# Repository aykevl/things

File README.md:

# Sandbox for electronics projects

This is my personal stash of small electronics projects, usually written using [TinyGo](https://tinygo.org).

I won't guarantee anything about it. All I can say is that it did work for me at some point and I like sharing what I made. Many things are written once and then mostly forgotten so I probably won't provide any support for any of the code.

## License

Feel free to use this code however you wish (in other words, you can treat it as public domain). Especially for small parts I won't mind if you just copy it in your project. For larger pieces of code or if you copy a project entirely, I would appreciate attribution somewhere (but it's not required).

If you prefer having an actual license for legal reasons, you can use the [MIT license](https://opensource.org/license/mit/) - but again, the code is public domain so no need to actually use this:

```
Copyright 2023 Ayke van Laethem

Permission is hereby granted, free of charge, to any person obtaining a
copy of this software and associated documentation files (the
“Software”), to deal in the Software without restriction, including
without limitation the rights to use, copy, modify, merge, publish,
distribute, sublicense, and/or sell copies of the Software, and to
permit persons to whom the Software is furnished to do so, subject to
the following conditions:

The above copyright notice and this permission notice shall be included
in all copies or substantial portions of the Software.

THE SOFTWARE IS PROVIDED “AS IS”, WITHOUT WARRANTY OF ANY KIND, EXPRESS
OR IMPLIED, INCLUDING BUT NOT LIMITED TO THE WARRANTIES OF
MERCHANTABILITY, FITNESS FOR A PARTICULAR PURPOSE AND NONINFRINGEMENT.
IN NO EVENT SHALL THE AUTHORS OR COPYRIGHT HOLDERS BE LIABLE FOR ANY
CLAIM, DAMAGES OR OTHER LIABILITY, WHETHER IN AN ACTION OF CONTRACT,
TORT OR OTHERWISE, ARISING FROM, OUT OF OR IN CONNECTION WITH THE
SOFTWARE OR THE USE OR OTHER DEALINGS IN THE SOFTWARE.
```

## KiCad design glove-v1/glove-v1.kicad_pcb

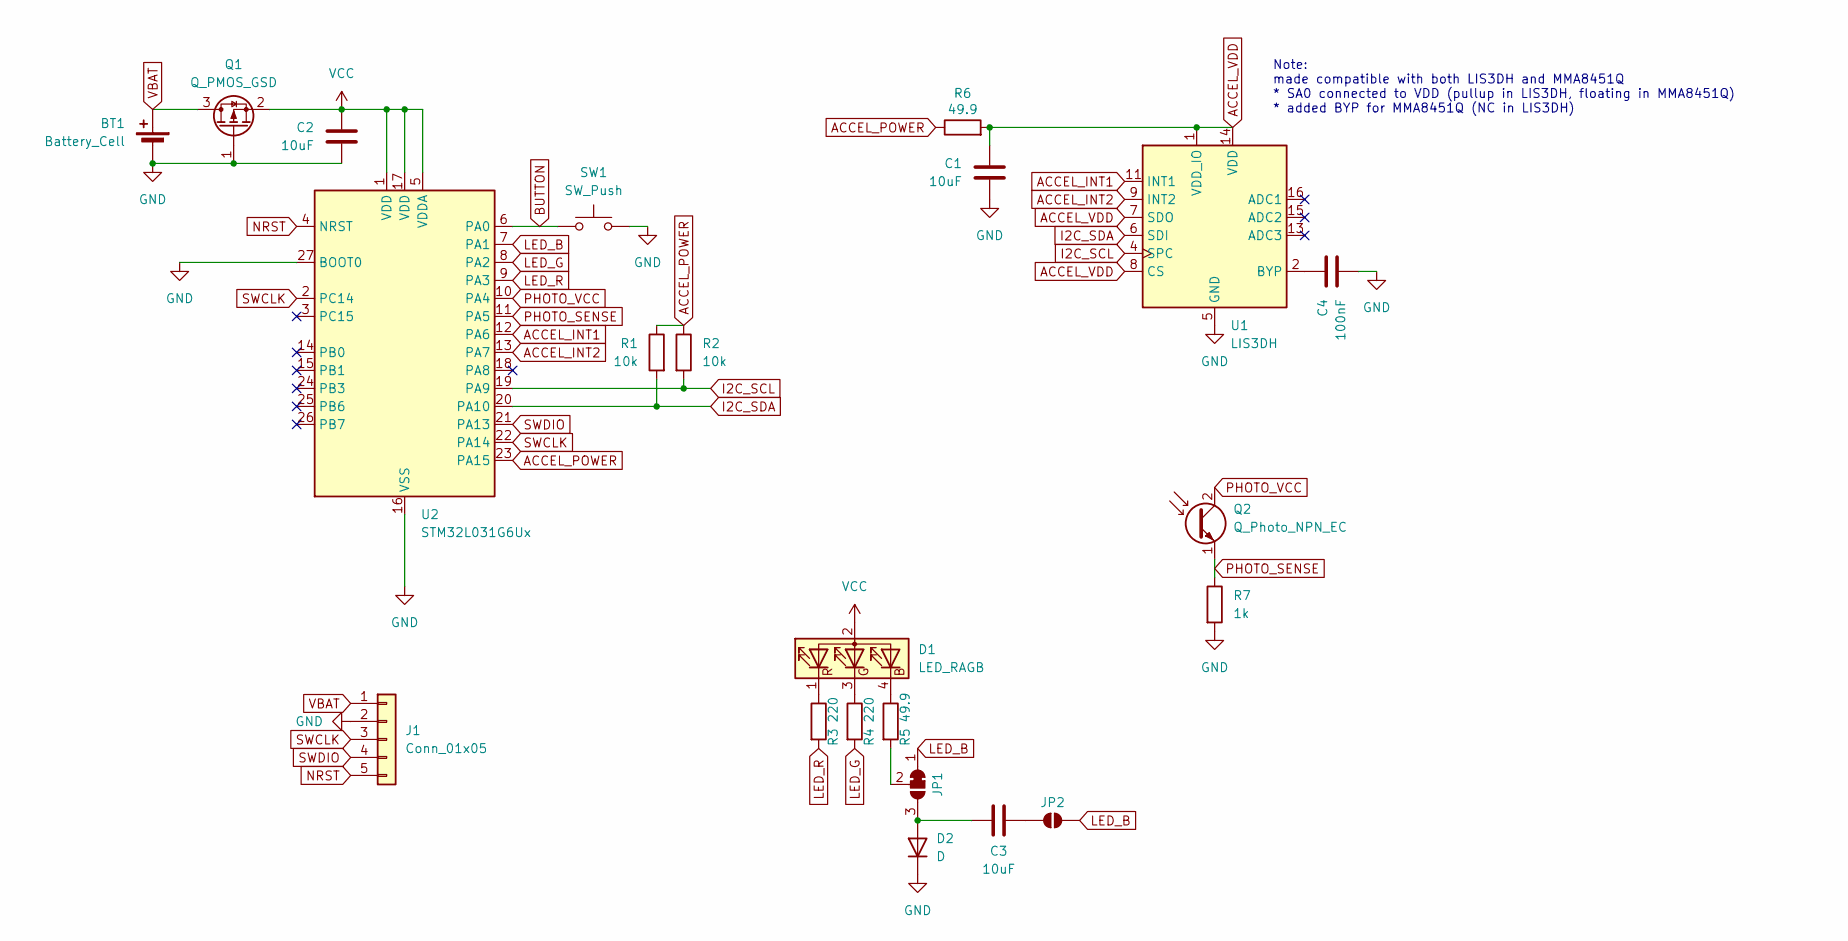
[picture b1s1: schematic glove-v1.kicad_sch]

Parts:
BT1: Battery_Cell; MY-1220-03; LCSC C964818
C1, C2, C3: 10uF; C_0402_1005Metric; LCSC C15525
C4: 100nF; C_0402_1005Metric; LCSC C1525
D1: LED_RAGB
D2: D; D_SOD-523; LCSC C2128
J1: Conn_01x05; ProgramHeader
JP1: SolderJumper-3_P1.3mm_Bridged12_RoundedPad1.0x1.5mm
JP2: SolderJumper-2_P1.3mm_Open_RoundedPad1.0x1.5mm
Q1: Q_PMOS_GSD; SOT-23; LCSC C427391
Q2: Q_Photo_NPN_EC; LED_0603_1608Metric; LCSC C20416370
R1, R2: 10k; R_0402_1005Metric; LCSC C25744
R3, R4: 220; R_0402_1005Metric; LCSC C25091
R5, R6: 49.9; R_0402_1005Metric; LCSC C25120
R7: 1k; R_0402_1005Metric; LCSC C11702
SW1: SW_Push; SW_Push_SPST_NO_Alps_SKRK; LCSC C720477
U1: LIS3DH; LGA-16_3x3mm_P0.5mm_LayoutBorder3x5y; LCSC C15134
U2: STM32L031G6Ux; QFN-28_4x4mm_P0.5mm; LCSC C96514

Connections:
ACCEL_INT1: U1.11 (INT1), U2.12 (PA6)
ACCEL_INT2: U1.9 (INT2), U2.13 (PA7)
ACCEL_POWER: R1.1, R2.1, R6.1, U2.23 (PA15)
ACCEL_VDD: C1.1, R6.2, U1.1 (VDD_IO), U1.7 (SDO), U1.8 (CS), U1.14 (VDD)
BUTTON: SW1.2, U2.6 (PA0)
GND: BT1.2 (-), C1.2, C2.2, C4.2, D2.1 (K), J1.2, Q1.1 (G), R7.2, SW1.1, U1.5 (GND), U1.10 (GND), U1.12 (GND), U2.16 (VSS), U2.27 (BOOT0), U2.28 (VSS)
I2C_SCL: R2.2, U1.4 (SPC), U2.19 (PA9)
I2C_SDA: R1.2, U1.6 (SDI), U2.20 (PA10)
LED_B: JP1.1 (A), JP2.2 (B), U2.7 (PA1)
LED_G: R4.2, U2.8 (PA2)
LED_R: R3.2, U2.9 (PA3)
NRST: J1.5, U2.4 (NRST)
unnamed: D1.4 (BK), R5.1
unnamed: D1.3 (GK), R4.1
unnamed: D1.1 (RK), R3.1
unnamed: C3.1, D2.2 (A), JP1.3 (B)
unnamed: JP1.2 (C), R5.2
unnamed: C3.2, JP2.1 (A)
unnamed: C4.1, U1.2 (BYP)
PHOTO_SENSE: Q2.1 (E), R7.1, U2.11 (PA5)
PHOTO_VCC: Q2.2 (C), U2.10 (PA4)
SWCLK: J1.3, U2.2 (PC14), U2.22 (PA14)
SWDIO: J1.4, U2.21 (PA13)
VBAT: BT1.1 (+), J1.1, Q1.3 (D)
VCC: C2.1, D1.2 (A), Q1.2 (S), U2.1 (VDD), U2.5 (VDDA), U2.17 (VDD)

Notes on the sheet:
Note: made compatible with both LIS3DH and MMA8451Q * SA0 connected to VDD (pullup in LIS3DH, floating in MMA8451Q) * added BYP for MMA8451Q (NC in LIS3DH)

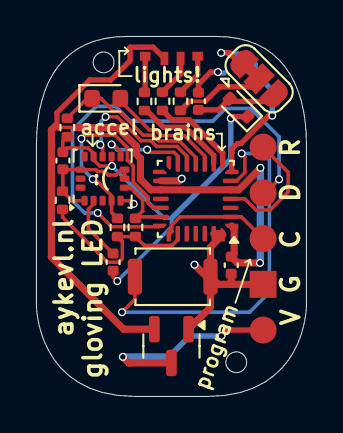
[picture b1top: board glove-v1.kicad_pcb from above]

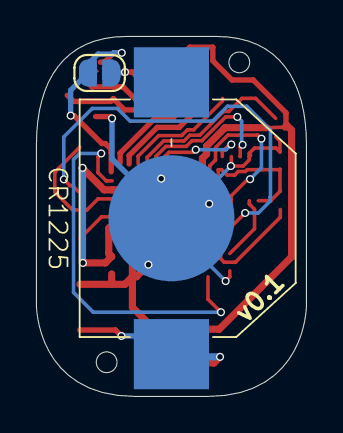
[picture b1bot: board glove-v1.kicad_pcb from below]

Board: 2 copper layers, 15.0 x 20.0 mm, 22 parts (2 on the bottom side), 25 nets.

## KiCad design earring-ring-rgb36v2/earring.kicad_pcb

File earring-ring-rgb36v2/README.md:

# 36-LED RGB earrings

These earrings are the successor to my previous [36-LED earrings](../earring-ring-rgb36). The main changes are the addition of a microphone and a second button. The software has also been greatly extended with many new animation patterns.

## Updating firmware

For writing the firmware, you will need an SWD programmer. Both [ST-Link](https://www.aliexpress.com/w/wholesale-st%2525252dlink-v2.html) and DAPLink programmers have been tested and work fine. You can even use a [Raspberry Pi Pico with a special firmware](https://github.com/raspberrypi/debugprobe/releases) as a [programmer](https://pip-assets.raspberrypi.com/categories/610-raspberry-pi-pico/documents/RP-008276-DS-1-getting-started-with-pico.pdf#page=19), use GP2 as SWCLK and GP3 as SWDIO.

You can connect the programmer as indicated on the PCB itself. Specifically:

  * Connect VCC to 3.3V, or don't connect it if you have a battery inserted (make sure to _never_ connect VCC when a battery is inserted!).
  * Connect GND to the programmer GND.
  * Connect SWC to the SWCLK pin on the programmer.
  * Connect SWD to the SWDIO pin on the programmer.

You normally don't need to connect RST, but it is exposed since it's possible to put the chip in a state where it doesn't respond to programming anymore an you need to briefly connect RST to GND to reset it.

I found the easiest way to program these earrings is using a clip with pogo-pins, like [this one](https://nl.aliexpress.com/item/1005006712952020.html) (2.54mm distance, single row, 4 or 5 pins depending on needs). It makes quick iteration much easier. However, you may also be able to hold the 3-4 wires manually to the right pads, use [stackable header pins](https://www.aliexpress.com/w/wholesale-stackable-header-pins.html) to more easily hold them there, or solder them.

Once everything is in place, you can update the firmware like this:

    openocd -f interface/stlink.cfg -f target/stm32l0.cfg -c 'program firmware.hex verify reset exit'

(Replace `stlink` with `cmsis-dap` if you have a DAPLink based programmer, which is most of them nowadays).

Alternatively, you can use [`probe-rs`](https://probe.rs/) which is a more modern tool:

    probe-rs download --verify --chip=STM32L031G6Ux --binary-format=hex firmware.hex

Some tips and tricks:

  * You may need to retry a few times, the earrings run at a low enough frequency that they don't always recognize a debug probe is trying to reach them. If it says `** Verified OK **` (OpenOCD) it was flashed correctly.
  * Double check the cables if things don't work, it's easy to miss a loose wire.
  * If all else fails, you can ask if someone at a nearby hackerspace wants to help you out. Or ask me if we meet at a hacker/chaos event - I will often carry a programmer with me.

## Modifying the firmware

You can change the firmware if you want for specific customizations not possible through [custom patterns](https://aykevl.nl/projects/earrings-rgb36v2#custom-patterns).

 1. Install [TinyGo](https://tinygo.org/getting-started/install/).
 2. Connect the wires and programmer as described above.
 3. Run the following command for programming (use `-programmer=cmsis-dap` if you are using a DAPLink programmer):

        tinygo flash -target=./stm32l0x1.json -opt=2 -panic=trap -programmer=stlink

It should flash the binary to the earring, though it might need a few tries - for some reason the low clock frequency of the chip makes flashing a little bit less reliable.

## Writing your own patterns

While these earrings support [custom patterns programmed through sound](https://aykevl.nl/projects/earrings-rgb36v2#custom-patterns), you may want to modify or add to the default set of patterns.

First we need to add a new mode constant:

```diff
 const (
 	modeTrace = iota
 	modeNoise
 	modeFire
 	modeFireSound
 	modeStatic
 	modeFlag
 	modeSparkle
 	modeVUMeter
+	modeCustom
```

You can also reorder/remove modes here if you want, as long as you keep the `= iota` on the first and keep `modeLast` at the end.

Next we add the mode to the `animate` function:

```go
func animate(mode, variant, led, frame int) Color {
	switch mode {
	...
	case modeCustom:
		return myCustomAnimation(led, frame)
	...
	}
}
```

And lastly we can write our own animation:

```go
func myCustomAnimation(led, frame int) Color {
	return NewColor(255, 0, 0)
}
```

How it works is that there are two parameters: the LED number (0..35) and the frame (running at about 30 frames per second, depending on the complexity of the animation). And the function just returns the RGB color for that particular LED, similar to a [pixel shader](https://en.wikipedia.org/wiki/Shader#Pixel_shaders). In this case we just return the static color red, but you can do more interesting things too! Here is an animation that rotates a single color around:

```go
func myCustomAnimation(led, frame int) Color {
	return NewColor(uint8((frame-led)%36)*4, 0, 0)
}
```

And here is a more advanced animation similar to the ["sparkle" mode of the HALO-90](https://github.com/openKolibri/halo-90/blob/master/readme.md#sparkle). It uses a [xorshift](https://en.wikipedia.org/wiki/Xorshift) function to achieve something that looks reasonably random:

```go
var xorshift32State uint32 = 1

// See https://en.wikipedia.org/wiki/Xorshift
func xorshift32() uint32 {
	xorshift32State ^= xorshift32State << 13
	xorshift32State ^= xorshift32State >> 17
	xorshift32State ^= xorshift32State << 5
	return xorshift32State
}

func myCustomAnimation(led, frame int) Color {
	if xorshift32()%16 == 0 {
		return NewColor(uint8(xorshift32()%64), 0, 0)
	}
	return NewColor(0, 0, 0)
}
```

You can also take a look at all the other animations in the file to get some ideas of what you can do. However, make sure to keep it simple! The earring is running at a low frequency and if the animation is too complex it will run slowly and the LEDs will be much dimmer.

## Version history

  * 2026-06-01: initial version
  * 2026-07-01: added [custom pattern feature](https://aykevl.nl/projects/earrings-rgb36v2#custom-patterns)

## Credits

I got a lot of inspiration from the earrings made by [California STEAM](https://www.tindie.com/stores/californiasteam/). Unfortunately they're not shipping to Europe so I had to make my own 🙂

Another cool project I found was [this earring on Hackaday](https://hackaday.io/project/186402-ws2812b-neopixel-earring). It's built quite differently however, even using WS2812 LEDs!

And after I made my [previous earrings](../earring-ring), I found these [MNT x Kolibri HALO-90 electronic earrings](https://shop.mntre.com/products/mnt-x-kolibri-halo-90-electronic-earrings) which inspired me to get even higher pixel counts. 18 LEDs just doesn't cut it anymore in 2025! They've definitely been an inspiration, though of course their choices in electronics and animation patterns are quite different.

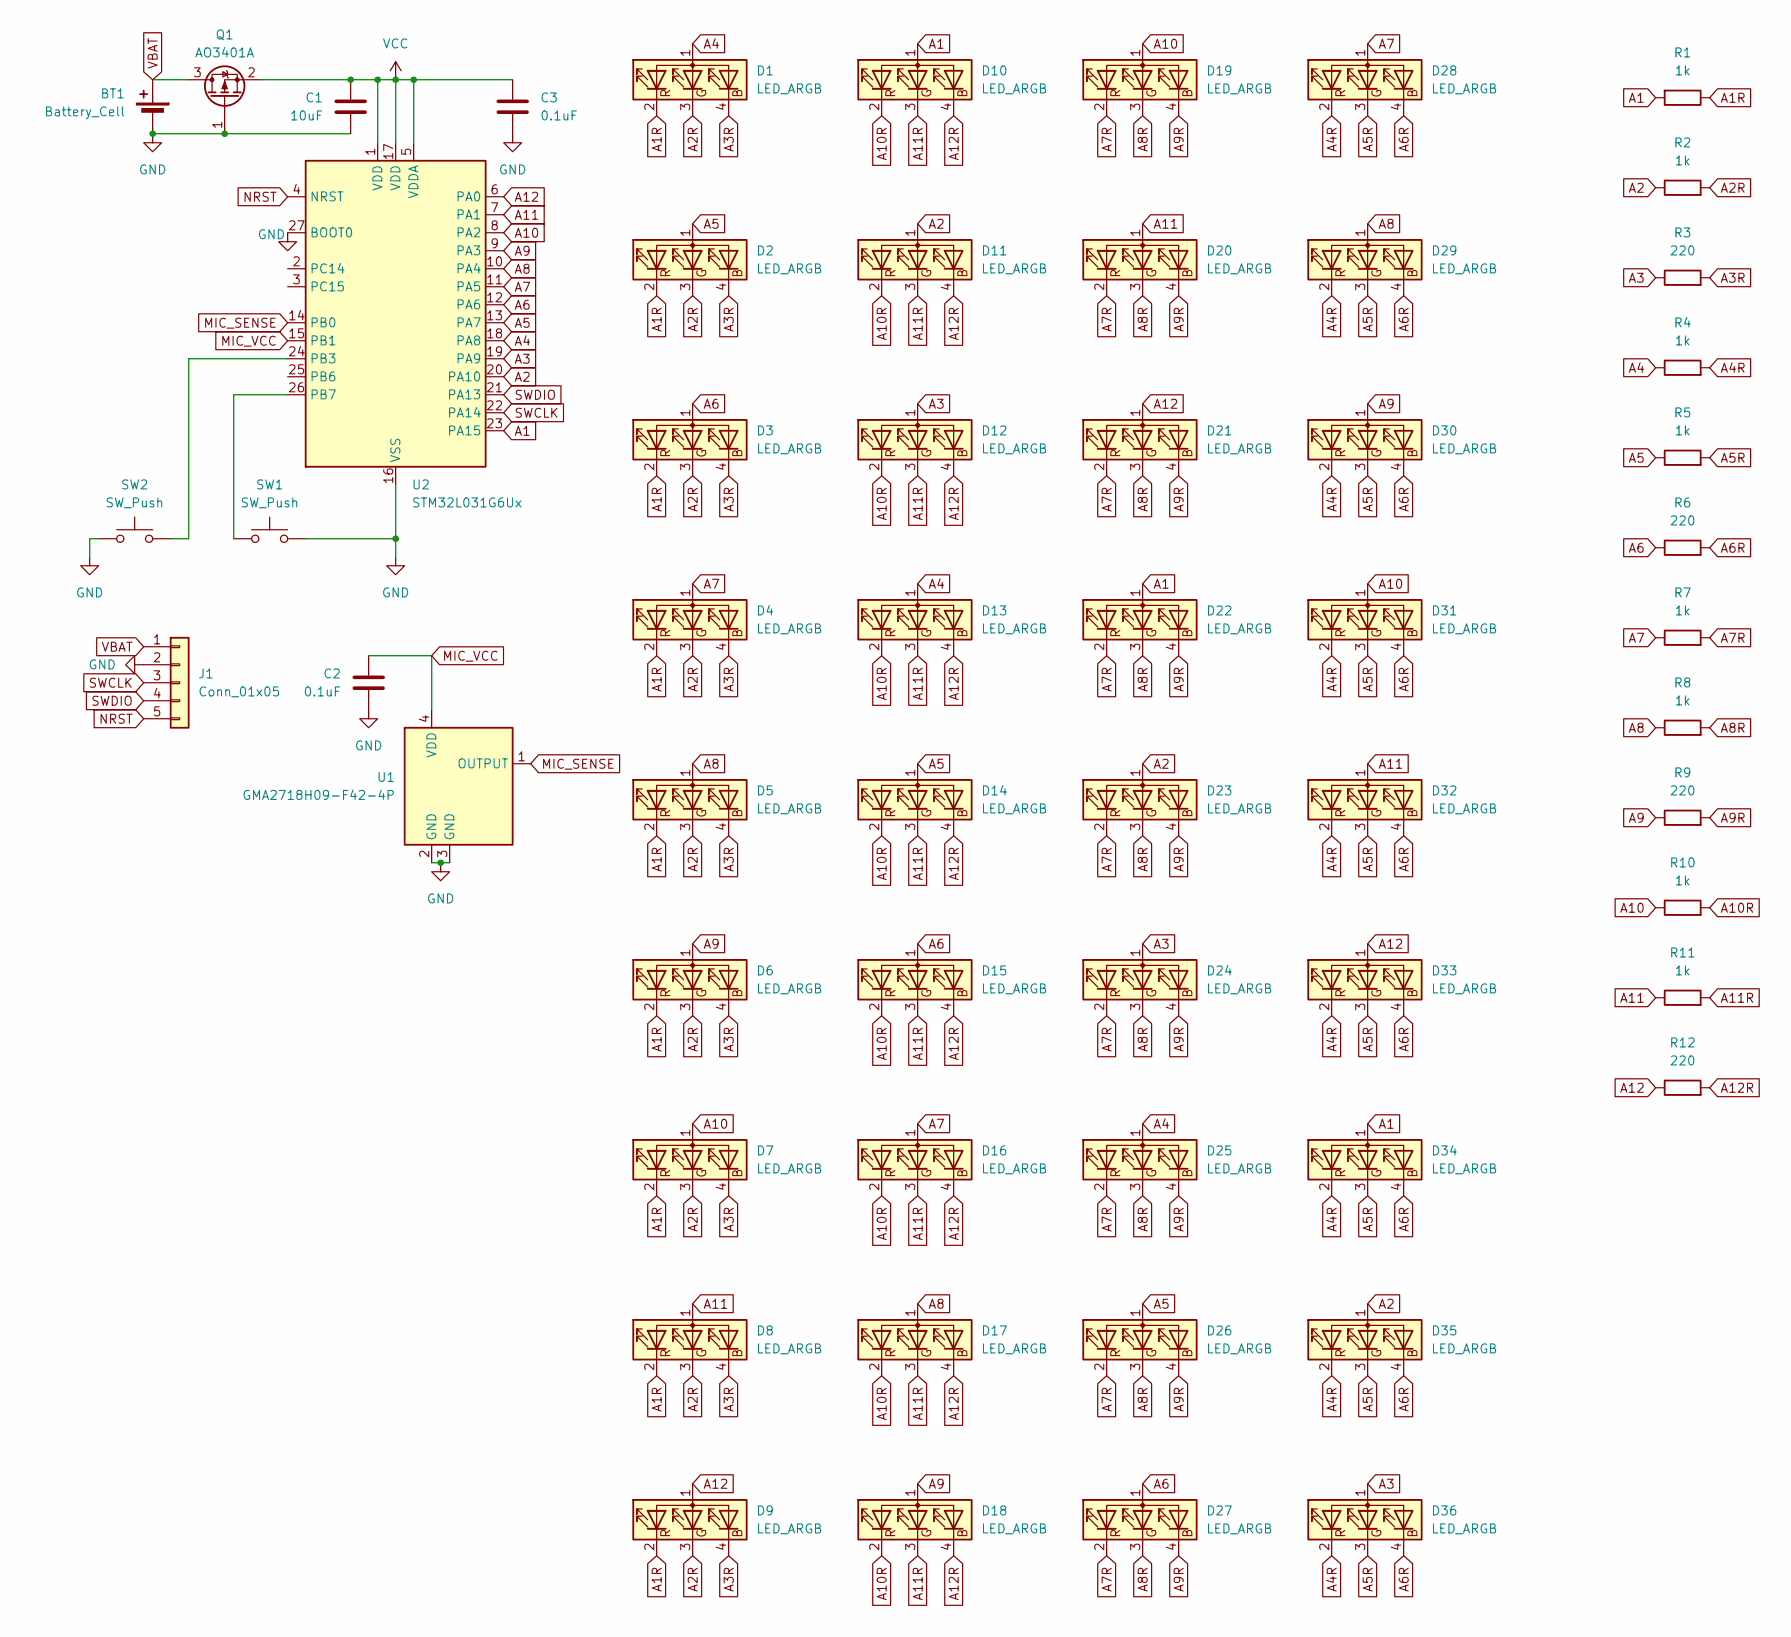
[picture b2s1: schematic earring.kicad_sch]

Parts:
BT1: Battery_Cell; MY-1220-03; LCSC C964818
C1: 10uF; C_0402_1005Metric; LCSC C15525
C2, C3: 0.1uF; C_0402_1005Metric; LCSC C1525
D1, D2, D3, D4, D5, D6, D7, D8, D9, D10, D11, D12, D13, D14, D15, D16, D17, D18, D19, D20, D21, D22, D23, D24, D25, D26, D27, D28, D29, D30, D31, D32, D33, D34, D35, D36: LED_ARGB; NH-Z1415RGBA-SG; LCSC C2874117
J1: Conn_01x05; ProgramHeader
Q1: AO3401A; SOT-23; LCSC C15127
R1, R2, R4, R5, R7, R8, R10, R11: 1k; R_0402_1005Metric; LCSC C11702
R3, R6, R9, R12: 220; R_0402_1005Metric; LCSC C25091
SW1, SW2: SW_Push; SW_Push_SPST_NO_Alps_SKRK; LCSC C561519
U1: GMA2718H09-F42-4P; LCSC C5142165
U2: STM32L031G6Ux; QFN-28_4x4mm_P0.5mm; LCSC C96514

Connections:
A1: D10.1 (A), D22.1 (A), D34.1 (A), R1.2, U2.23 (PA15)
A1R: D1.2 (RK), D2.2 (RK), D3.2 (RK), D4.2 (RK), D5.2 (RK), D6.2 (RK), D7.2 (RK), D8.2 (RK), D9.2 (RK), R1.1
A2: D11.1 (A), D23.1 (A), D35.1 (A), R2.1, U2.20 (PA10)
A2R: D1.3 (GK), D2.3 (GK), D3.3 (GK), D4.3 (GK), D5.3 (GK), D6.3 (GK), D7.3 (GK), D8.3 (GK), D9.3 (GK), R2.2
A3: D12.1 (A), D24.1 (A), D36.1 (A), R3.1, U2.19 (PA9)
A3R: D1.4 (BK), D2.4 (BK), D3.4 (BK), D4.4 (BK), D5.4 (BK), D6.4 (BK), D7.4 (BK), D8.4 (BK), D9.4 (BK), R3.2
A4: D1.1 (A), D13.1 (A), D25.1 (A), R4.1, U2.18 (PA8)
A4R: D28.2 (RK), D29.2 (RK), D30.2 (RK), D31.2 (RK), D32.2 (RK), D33.2 (RK), D34.2 (RK), D35.2 (RK), D36.2 (RK), R4.2
A5: D2.1 (A), D14.1 (A), D26.1 (A), R5.1, U2.13 (PA7)
A5R: D28.3 (GK), D29.3 (GK), D30.3 (GK), D31.3 (GK), D32.3 (GK), D33.3 (GK), D34.3 (GK), D35.3 (GK), D36.3 (GK), R5.2
A6: D3.1 (A), D15.1 (A), D27.1 (A), R6.1, U2.12 (PA6)
A6R: D28.4 (BK), D29.4 (BK), D30.4 (BK), D31.4 (BK), D32.4 (BK), D33.4 (BK), D34.4 (BK), D35.4 (BK), D36.4 (BK), R6.2
A7: D4.1 (A), D16.1 (A), D28.1 (A), R7.1, U2.11 (PA5)
A7R: D19.2 (RK), D20.2 (RK), D21.2 (RK), D22.2 (RK), D23.2 (RK), D24.2 (RK), D25.2 (RK), D26.2 (RK), D27.2 (RK), R7.2
A8: D5.1 (A), D17.1 (A), D29.1 (A), R8.1, U2.10 (PA4)
A8R: D19.3 (GK), D20.3 (GK), D21.3 (GK), D22.3 (GK), D23.3 (GK), D24.3 (GK), D25.3 (GK), D26.3 (GK), D27.3 (GK), R8.2
A9: D6.1 (A), D18.1 (A), D30.1 (A), R9.1, U2.9 (PA3)
A9R: D19.4 (BK), D20.4 (BK), D21.4 (BK), D22.4 (BK), D23.4 (BK), D24.4 (BK), D25.4 (BK), D26.4 (BK), D27.4 (BK), R9.2
A10: D7.1 (A), D19.1 (A), D31.1 (A), R10.1, U2.8 (PA2)
A10R: D10.2 (RK), D11.2 (RK), D12.2 (RK), D13.2 (RK), D14.2 (RK), D15.2 (RK), D16.2 (RK), D17.2 (RK), D18.2 (RK), R10.2
A11: D8.1 (A), D20.1 (A), D32.1 (A), R11.1, U2.7 (PA1)
A11R: D10.3 (GK), D11.3 (GK), D12.3 (GK), D13.3 (GK), D14.3 (GK), D15.3 (GK), D16.3 (GK), D17.3 (GK), D18.3 (GK), R11.2
A12: D9.1 (A), D21.1 (A), D33.1 (A), R12.1, U2.6 (PA0)
A12R: D10.4 (BK), D11.4 (BK), D12.4 (BK), D13.4 (BK), D14.4 (BK), D15.4 (BK), D16.4 (BK), D17.4 (BK), D18.4 (BK), R12.2
GND: BT1.2 (-), C1.2, C2.2, C3.2, J1.2, Q1.1 (G), SW1.1, SW2.1, U1.2 (GND), U1.3 (GND), U2.16 (VSS), U2.27 (BOOT0), U2.28 (VSS)
MIC_SENSE: U1.1 (OUTPUT), U2.14 (PB0)
MIC_VCC: C2.1, U1.4 (VDD), U2.15 (PB1)
NRST: J1.5, U2.4 (NRST)
unnamed: SW2.2, U2.24 (PB3)
unnamed: SW1.2, U2.26 (PB7)
SWCLK: J1.3, U2.22 (PA14)
SWDIO: J1.4, U2.21 (PA13)
VBAT: BT1.1 (+), J1.1, Q1.3 (D)
VCC: C1.1, C3.1, Q1.2 (S), U2.1 (VDD), U2.5 (VDDA), U2.17 (VDD)

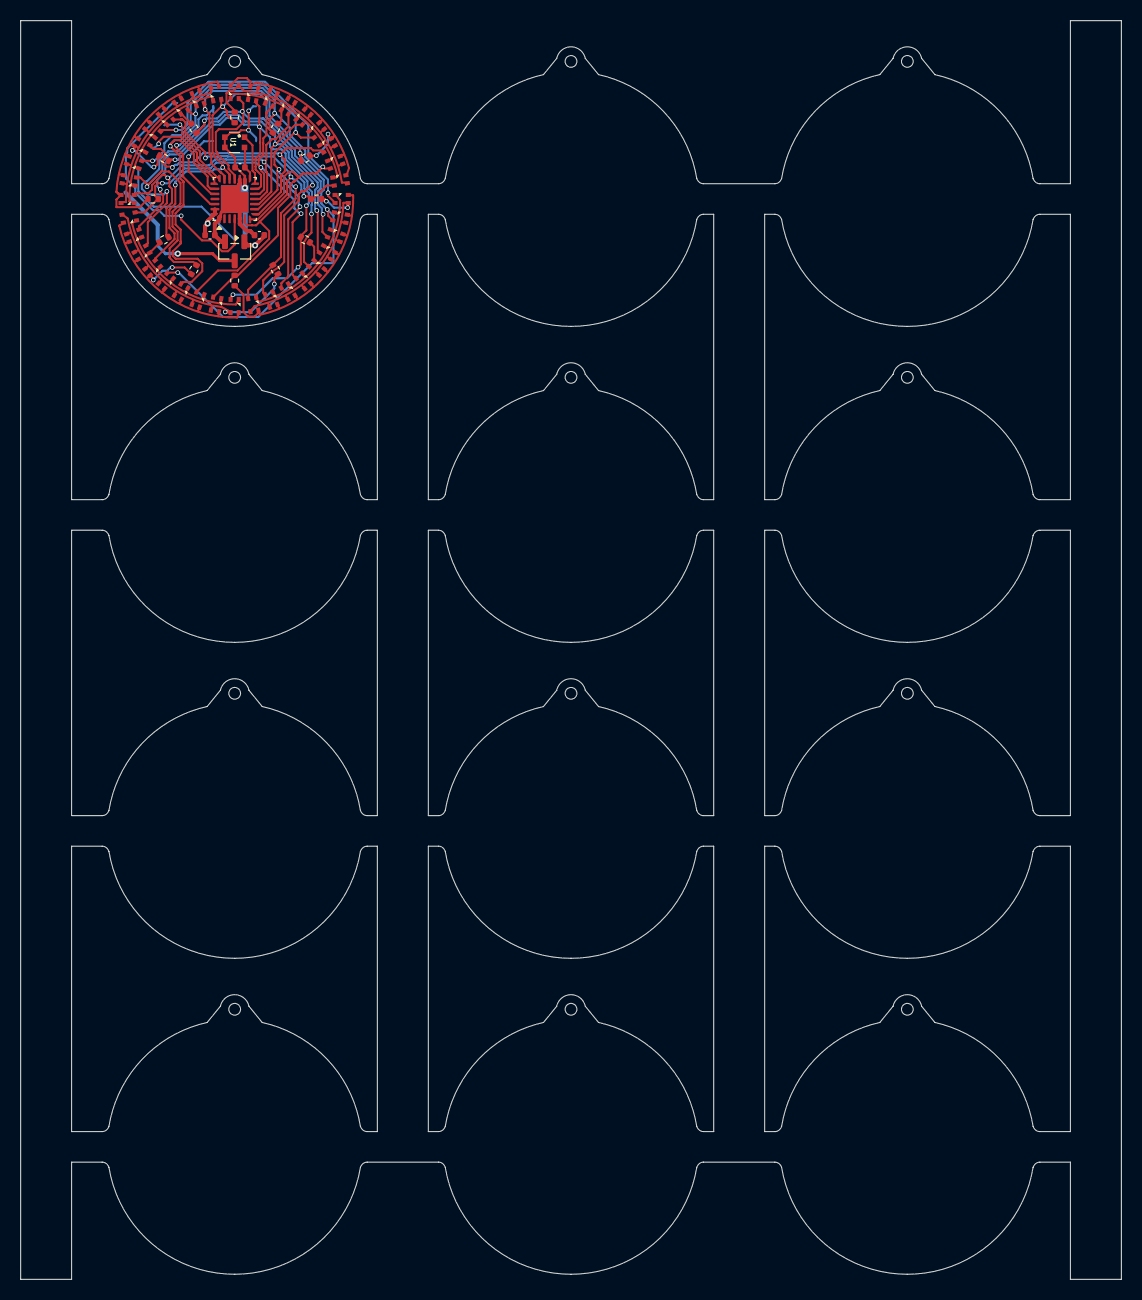
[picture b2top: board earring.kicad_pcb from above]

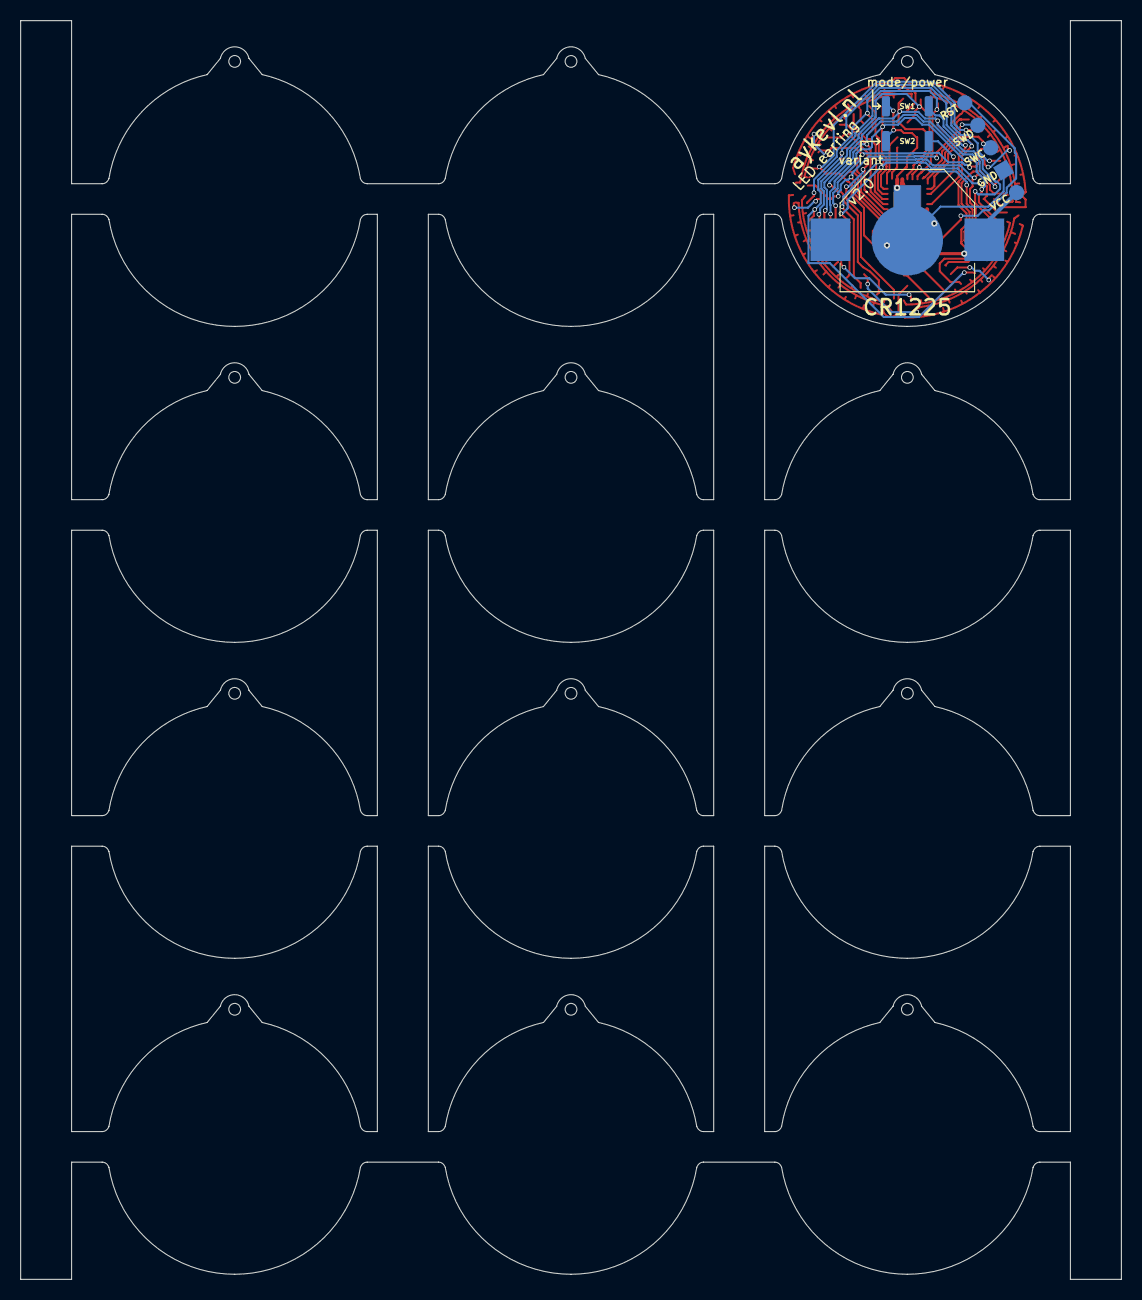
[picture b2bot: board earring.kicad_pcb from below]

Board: 2 copper layers, 108.0 x 123.5 mm, 70 parts (4 on the bottom side), 34 nets.

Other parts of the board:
H1, H1#2, H1#3, H1#4, H1#5, H1#6, H1#7, H1#8, H1#9, H1#10, H1#11, H1#12: ToolingHole; ToolingHole_JLCPCB

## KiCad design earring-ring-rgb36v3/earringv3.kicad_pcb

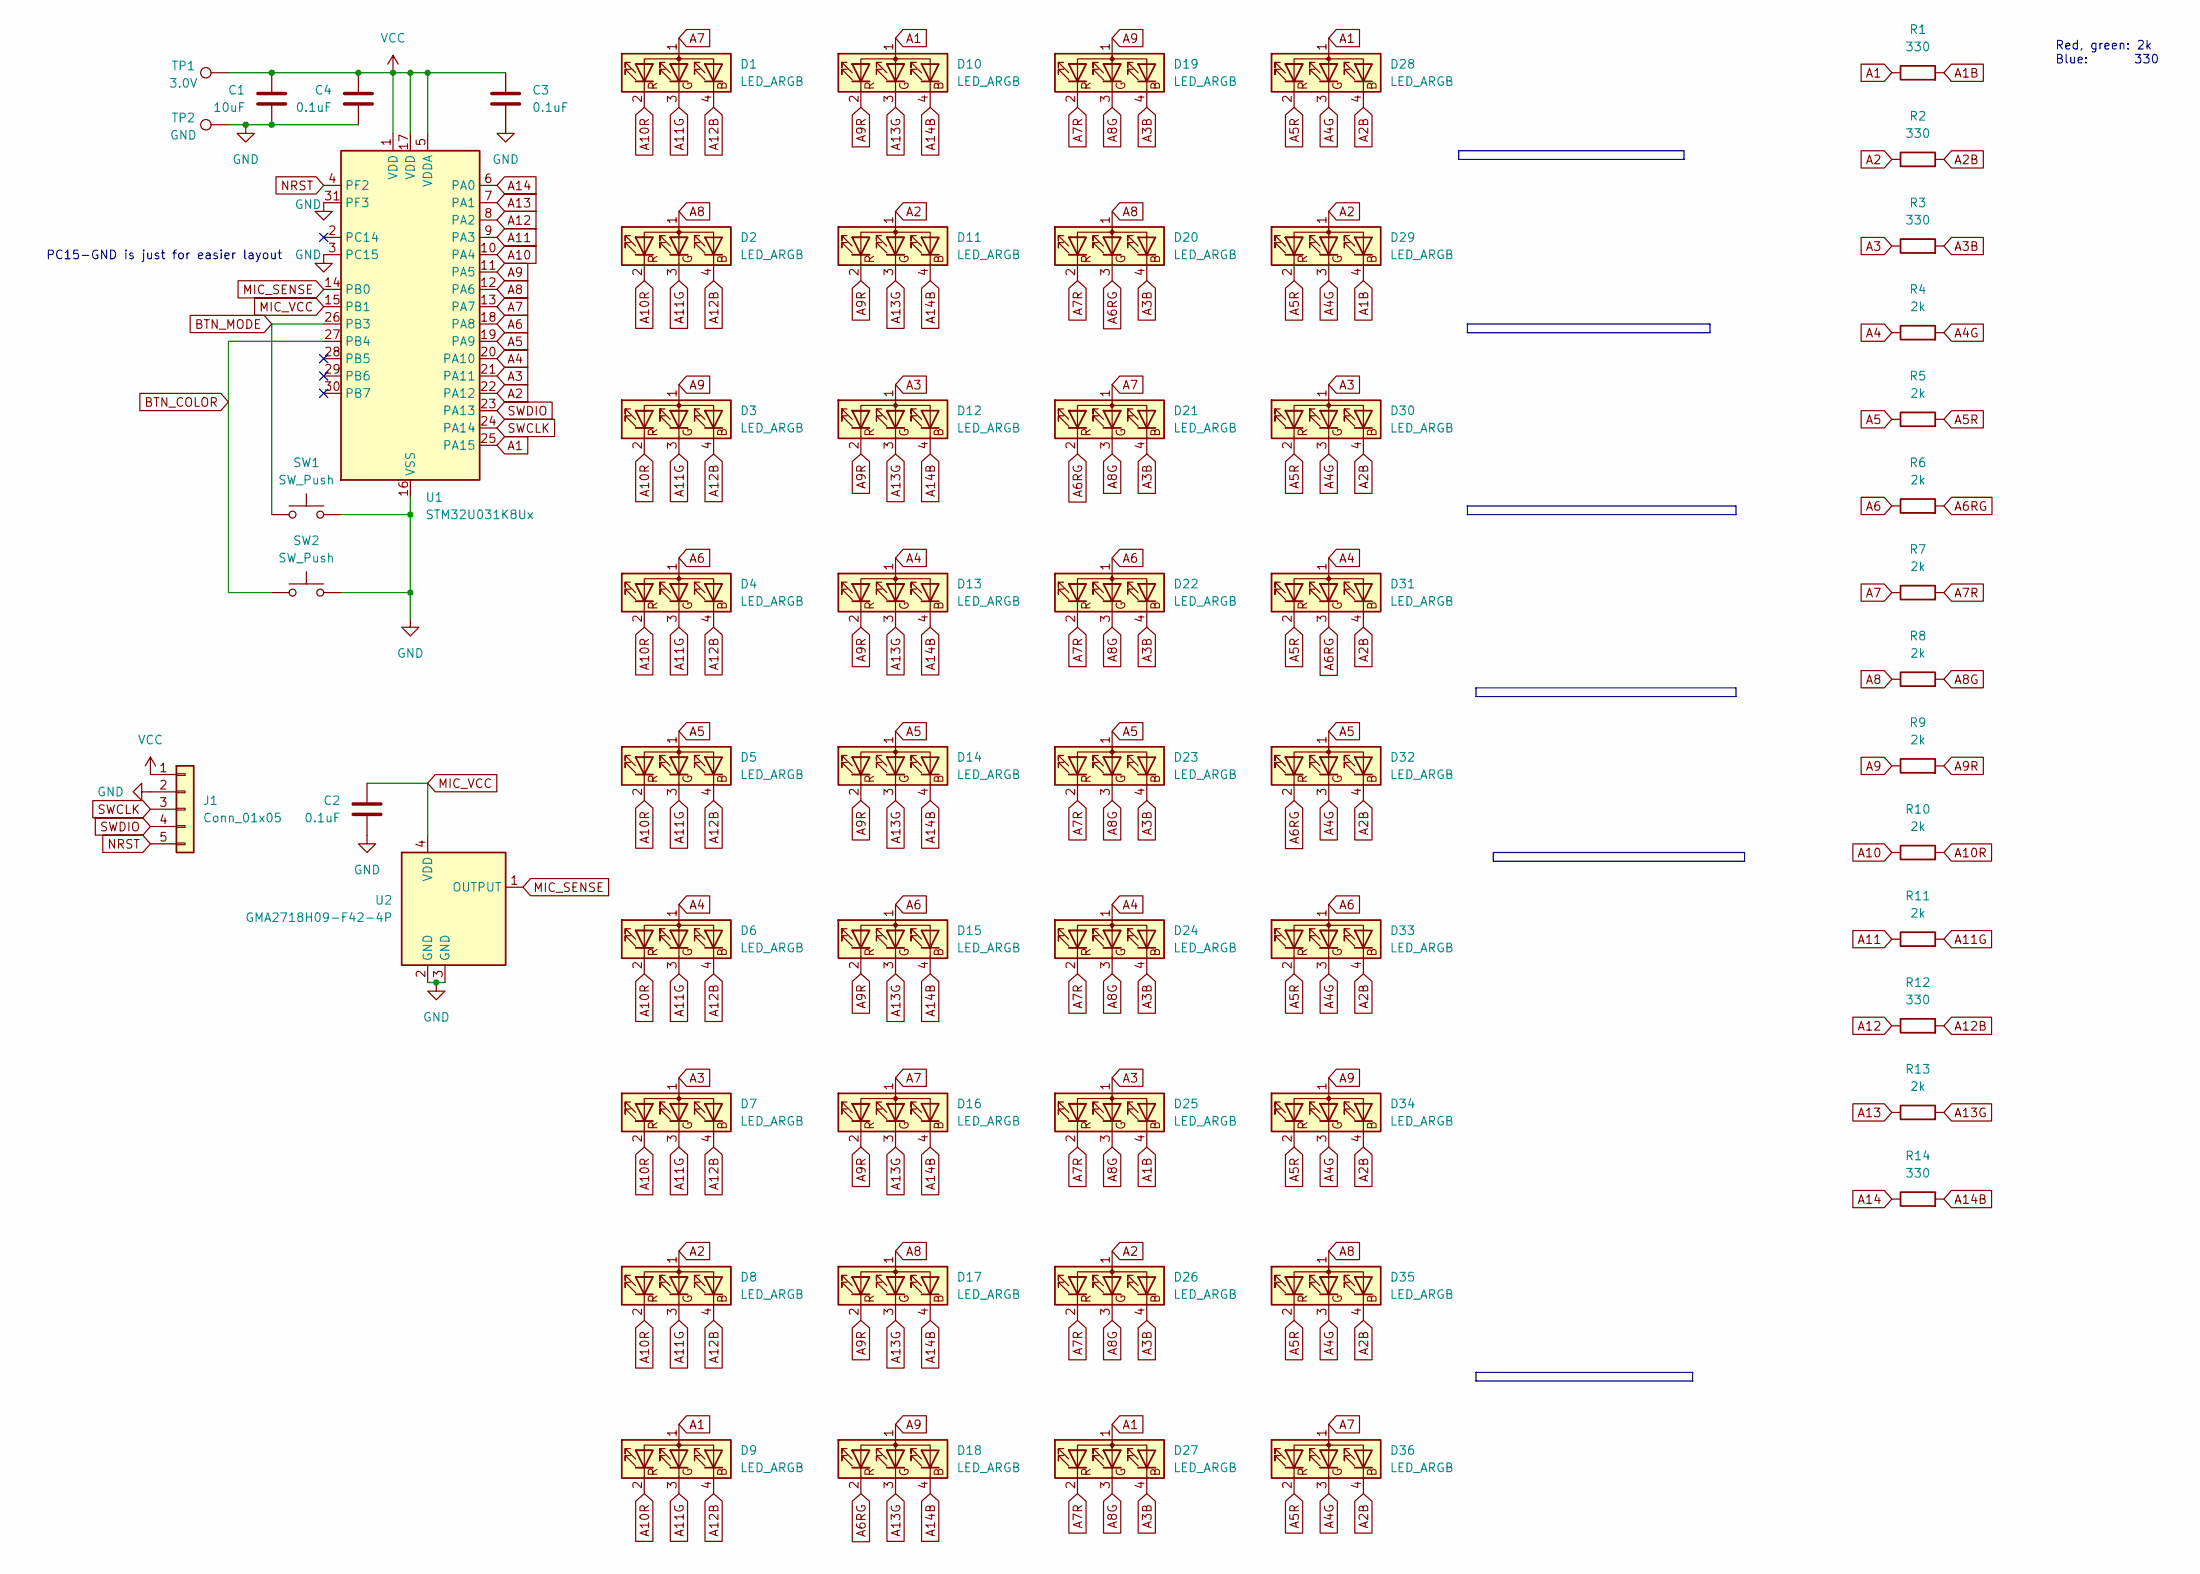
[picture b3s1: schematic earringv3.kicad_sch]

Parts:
C1: 10uF; C_0402_1005Metric; LCSC C15525
C2, C3, C4: 0.1uF; C_0402_1005Metric; LCSC C1525
D1, D2, D3, D4, D5, D6, D7, D8, D9, D10, D11, D12, D13, D14, D15, D16, D17, D18, D19, D20, D21, D22, D23, D24, D25, D26, D27, D28, D29, D30, D31, D32, D33, D34, D35, D36: LED_ARGB; NH-Z1415RGBA-SG; LCSC C2874117
J1: Conn_01x05; ProgramHeader
R1, R2, R3, R12, R14: 330; R_0402_1005Metric; LCSC C25104
R4, R5, R6, R7, R8, R9, R10, R11, R13: 2k; R_0402_1005Metric; LCSC C4109
SW1, SW2: SW_Push; SW_Push_SPST_NO_Alps_SKRK; LCSC C720477
TP1: 3.0V; TestPoint_Pad_1.5x1.5mm
TP2: GND; TestPoint_Pad_1.5x1.5mm
U1: STM32U031K8Ux; QFN-32-1EP_5x5mm_P0.5mm_EP3.45x3.45mm; LCSC C22445362
U2: GMA2718H09-F42-4P; LCSC C5142165

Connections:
A1: D9.1 (A), D10.1 (A), D27.1 (A), D28.1 (A), R1.1, U1.25 (PA15)
A1B: D25.4 (BK), D29.4 (BK), R1.2
A2: D8.1 (A), D11.1 (A), D26.1 (A), D29.1 (A), R2.1, U1.22 (PA12)
A2B: D28.4 (BK), D30.4 (BK), D31.4 (BK), D32.4 (BK), D33.4 (BK), D34.4 (BK), D35.4 (BK), D36.4 (BK), R2.2
A3: D7.1 (A), D12.1 (A), D25.1 (A), D30.1 (A), R3.1, U1.21 (PA11)
A3B: D19.4 (BK), D20.4 (BK), D21.4 (BK), D22.4 (BK), D23.4 (BK), D24.4 (BK), D26.4 (BK), D27.4 (BK), R3.2
A4: D6.1 (A), D13.1 (A), D24.1 (A), D31.1 (A), R4.1, U1.20 (PA10)
A4G: D28.3 (GK), D29.3 (GK), D30.3 (GK), D32.3 (GK), D33.3 (GK), D34.3 (GK), D35.3 (GK), D36.3 (GK), R4.2
A5: D5.1 (A), D14.1 (A), D23.1 (A), D32.1 (A), R5.1, U1.19 (PA9)
A5R: D28.2 (RK), D29.2 (RK), D30.2 (RK), D31.2 (RK), D33.2 (RK), D34.2 (RK), D35.2 (RK), D36.2 (RK), R5.2
A6: D4.1 (A), D15.1 (A), D22.1 (A), D33.1 (A), R6.1, U1.18 (PA8)
A6RG: D18.2 (RK), D20.3 (GK), D21.2 (RK), D31.3 (GK), D32.2 (RK), R6.2
A7: D1.1 (A), D16.1 (A), D21.1 (A), D36.1 (A), R7.1, U1.13 (PA7)
A7R: D19.2 (RK), D20.2 (RK), D22.2 (RK), D23.2 (RK), D24.2 (RK), D25.2 (RK), D26.2 (RK), D27.2 (RK), R7.2
A8: D2.1 (A), D17.1 (A), D20.1 (A), D35.1 (A), R8.1, U1.12 (PA6)
A8G: D19.3 (GK), D21.3 (GK), D22.3 (GK), D23.3 (GK), D24.3 (GK), D25.3 (GK), D26.3 (GK), D27.3 (GK), R8.2
A9: D3.1 (A), D18.1 (A), D19.1 (A), D34.1 (A), R9.1, U1.11 (PA5)
A9R: D10.2 (RK), D11.2 (RK), D12.2 (RK), D13.2 (RK), D14.2 (RK), D15.2 (RK), D16.2 (RK), D17.2 (RK), R9.2
A10: R10.1, U1.10 (PA4)
A10R: D1.2 (RK), D2.2 (RK), D3.2 (RK), D4.2 (RK), D5.2 (RK), D6.2 (RK), D7.2 (RK), D8.2 (RK), D9.2 (RK), R10.2
A11: R11.1, U1.9 (PA3)
A11G: D1.3 (GK), D2.3 (GK), D3.3 (GK), D4.3 (GK), D5.3 (GK), D6.3 (GK), D7.3 (GK), D8.3 (GK), D9.3 (GK), R11.2
A12: R12.1, U1.8 (PA2)
A12B: D1.4 (BK), D2.4 (BK), D3.4 (BK), D4.4 (BK), D5.4 (BK), D6.4 (BK), D7.4 (BK), D8.4 (BK), D9.4 (BK), R12.2
A13: R13.1, U1.7 (PA1)
A13G: D10.3 (GK), D11.3 (GK), D12.3 (GK), D13.3 (GK), D14.3 (GK), D15.3 (GK), D16.3 (GK), D17.3 (GK), D18.3 (GK), R13.2
A14: R14.1, U1.6 (PA0)
A14B: D10.4 (BK), D11.4 (BK), D12.4 (BK), D13.4 (BK), D14.4 (BK), D15.4 (BK), D16.4 (BK), D17.4 (BK), D18.4 (BK), R14.2
BTN_COLOR: SW2.2, U1.27 (PB4)
BTN_MODE: SW1.2, U1.26 (PB3)
GND: C1.2, C2.2, C3.2, C4.2, J1.2, SW1.1, SW2.1, TP2.1, U1.3 (PC15), U1.16 (VSS), U1.31 (PF3), U1.32 (VSS), U1.33 (VSS), U2.2 (GND), U2.3 (GND)
MIC_SENSE: U1.14 (PB0), U2.1 (OUTPUT)
MIC_VCC: C2.1, U1.15 (PB1), U2.4 (VDD)
NRST: J1.5, U1.4 (PF2)
SWCLK: J1.3, U1.24 (PA14)
SWDIO: J1.4, U1.23 (PA13)
VCC: C1.1, C3.1, C4.1, J1.1, TP1.1, U1.1 (VDD), U1.5 (VDDA), U1.17 (VDD)

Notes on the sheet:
PC15-GND is just for easier layout
Red, green: 2k Blue: 330

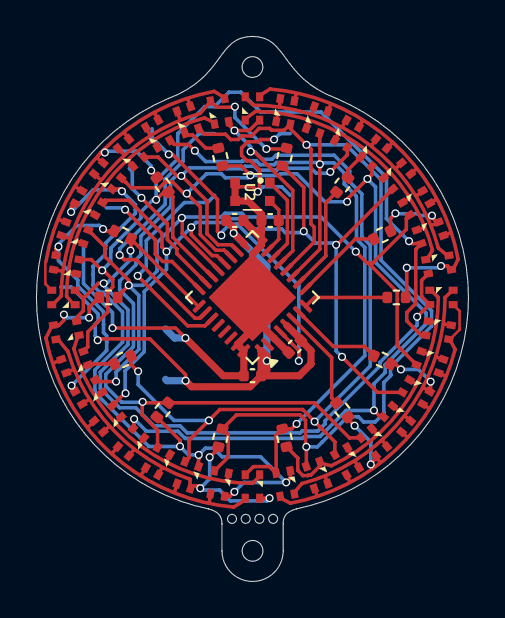
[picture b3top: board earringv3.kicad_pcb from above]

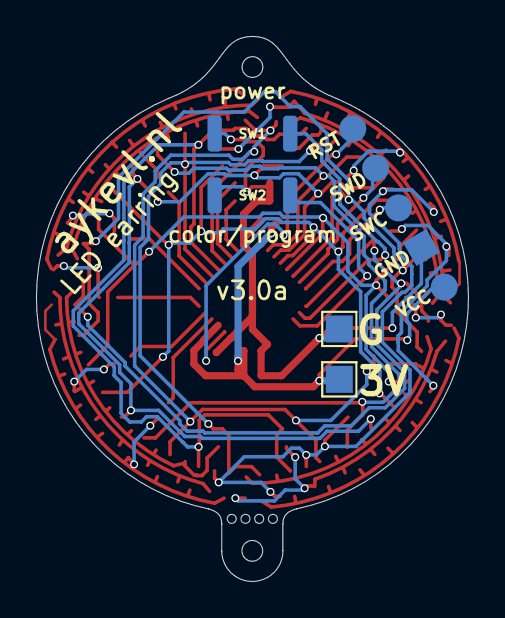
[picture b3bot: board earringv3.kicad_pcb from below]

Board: 2 copper layers, 24.0 x 30.3 mm, 62 parts (5 on the bottom side), 37 nets.

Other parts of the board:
H1: ToolingHole; ToolingHole_JLCPCB
